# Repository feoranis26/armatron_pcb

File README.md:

## ARMATRON pcb
PCB prototype files for ARMATRON

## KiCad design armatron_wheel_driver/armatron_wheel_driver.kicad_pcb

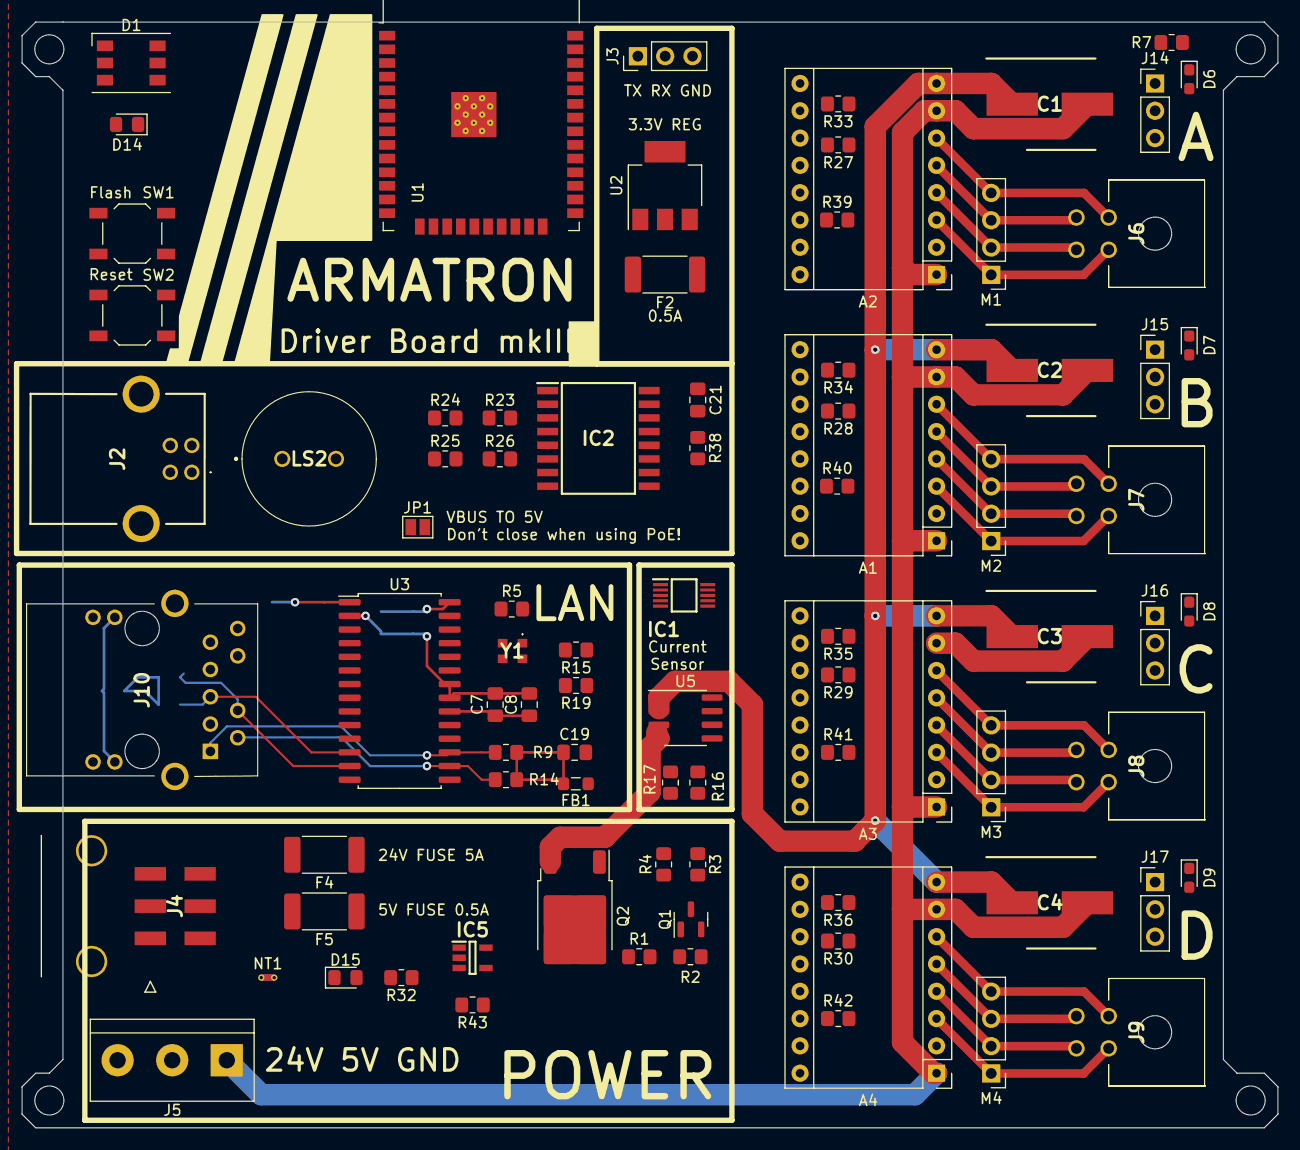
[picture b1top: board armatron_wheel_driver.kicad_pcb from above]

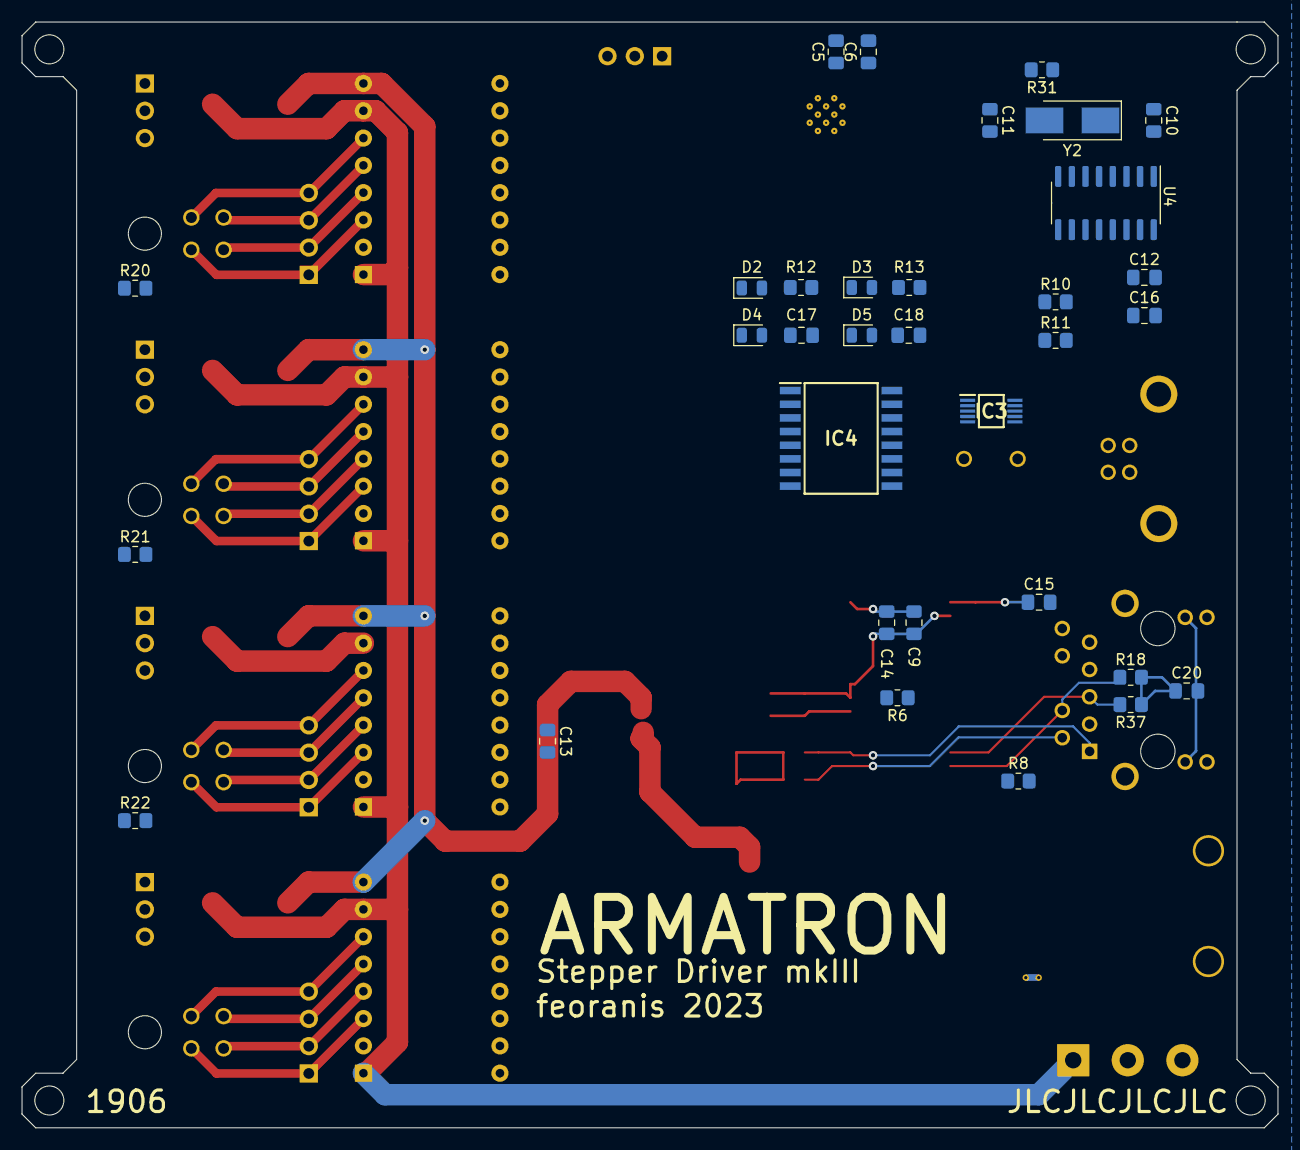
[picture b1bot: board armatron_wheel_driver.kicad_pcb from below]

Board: 2 copper layers, 116.8 x 102.9 mm, 123 parts (33 on the bottom side), 108 nets.

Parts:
A1, A2, A3, A4: Pololu_Breakout_DRV8825; Pololu_Breakout-16_15.2x20.3mm
C1, C2, C3, C4: C; CAPAE850X1050N
C5, C21: 10u; C_0805_2012Metric_Pad1.18x1.45mm_HandSolder
C6, C7, C9, C16, C17, C18: 100n; C_0805_2012Metric_Pad1.18x1.45mm_HandSolder
C8, C14, C15: 10uF; C_0805_2012Metric_Pad1.18x1.45mm_HandSolder
C10, C11: 22pF; C_0805_2012Metric_Pad1.18x1.45mm_HandSolder
C12: 4.7u; C_0805_2012Metric_Pad1.18x1.45mm_HandSolder
C13: 1n; C_0805_2012Metric_Pad1.18x1.45mm_HandSolder
C19, C20: 0.1uF; C_0805_2012Metric_Pad1.18x1.45mm_HandSolder
D1: Inolux_IN-PI556FCH; LED_WS2812_PLCC6_5.0x5.0mm_P1.6mm
D2, D3, D4, D5: D; D_0805_2012Metric
D6, D7, D8, D9: LED; LED_0603_1608Metric_Pad1.05x0.95mm_HandSolder
D14, D15: LED_Small; LED_0805_2012Metric_Pad1.15x1.40mm_HandSolder
F2, F5: 0.5A; Fuse_2512_6332Metric_Pad1.52x3.35mm_HandSolder
F4: 5A; Fuse_2512_6332Metric_Pad1.52x3.35mm_HandSolder
FB1: FerriteBead_Small; L_0805_2012Metric_Pad1.05x1.20mm_HandSolder
H1, H2, H3, H4: MountingHole; MountingHole_2.7mm_M2.5
IC1: ADS1115BQDGSRQ1; SOP50P490X110-10N
IC2, IC4: PCF8574T_3,518; SOIC127P1032X265-16N
IC3: MAX4634EUB+; SOP50P490X110-10N
IC5: M74VHC1GT50DTT1G; SOT95P275X110-5N
J2: USB_B; USB1030GFPBB
J3: Conn_01x03_Pin; PinHeader_1x03_P2.54mm_Vertical
J4: 43045-0606; 43045-06YY_060708_1
J5: Screw_Terminal_01x03; TerminalBlock_bornier-3_P5.08mm
J6, J7, J8, J9: 3-794620-4; 37946204
J10: 74982104400
J14, J15, J16, J17: Conn_01x03_Socket; PinHeader_1x03_P2.54mm_Vertical
JP1: SolderJumper_2_Open; SolderJumper-2_P1.3mm_Open_Pad1.0x1.5mm
LS2: PT-1241PFQ; PT1241PFQ
M1, M2, M3, M4: 17HS4401; PinHeader_1x04_P2.54mm_Vertical
NT1: NetTie_2; NetTie-2_THT_Pad0.3mm
Q1: BC817; SOT-23
Q2: Q_PNP_Darlington_BCE; TO-252-2
R1: 100K; R_0805_2012Metric_Pad1.20x1.40mm_HandSolder
R2, R3, R4, R7, R20, R21, R22, R23, R24, R25, R26, R27, R28, R29, R30, R31, R32, R33, R34, R35, R36, R38, R39, R40, R41, R42, R43: 1K; R_0805_2012Metric_Pad1.20x1.40mm_HandSolder
R5, R6, R10, R11, R12, R13: 10K; R_0805_2012Metric_Pad1.20x1.40mm_HandSolder
R8: 2.32K 1%; R_0805_2012Metric_Pad1.20x1.40mm_HandSolder
R9, R14, R18, R37: 50R; R_0805_2012Metric_Pad1.20x1.40mm_HandSolder
R15, R19: 220R; R_0805_2012Metric_Pad1.20x1.40mm_HandSolder
R16: 220K; R_0805_2012Metric_Pad1.20x1.40mm_HandSolder
R17: 27K; R_0805_2012Metric_Pad1.20x1.40mm_HandSolder
SW1, SW2: SW_Push; SW_SPST_TL3342
U1: ESP32-WROOM-32
U2: AMS1117-3.3; SOT-223-3_TabPin2
U3: ENC28J60x-SO; SOIC-28W_7.5x17.9mm_P1.27mm
U4: CH340G; SOIC-16_3.9x9.9mm_P1.27mm
U5: ACS712xLCTR-20A; SOIC-8_3.9x4.9mm_P1.27mm
Y1: ECS-2520MVLC-250-BN-TR3; ECS2520MVLC250BNTR3
Y2: 12MHz; Crystal_SMD_5032-2Pin_5.0x3.2mm_HandSoldering

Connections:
+3.3V: C5.1, C6.1, C7.1, C8.1, C9.1, C12.1, C14.1, C16.1, C21.1, D6.2 (A), D7.2 (A), D8.2 (A), D9.2 (A), D14.2 (A), F2.2, FB1.1, IC1.8 (VDD), IC2.16 (VDD), IC3.5 (EN), IC3.6 (V+), IC4.1 (A0), IC4.16 (VDD), IC5.5 (VCC), R5.1, R12.1, R13.1, R23.1, R24.1, R25.1, R26.1, R27.1, R28.1, R29.1, R30.1, R32.1, R38.1, R39.2, R40.2, R41.2, R42.2, R43.1, U1.2 (VDD), U3.15 (VDDTX), U3.19 (VDDRX), U3.20 (VDDPLL), U3.25 (VDDOSC), U3.28 (VDD), U4.4 (V3), U4.16 (VCC), Y1.4 (VDD)
+5V: D1.3 (VDD), D1.5 (VCC), F5.1, J5.2, J10.9 (V2+), J14.2, J15.2, J16.2, J17.2, JP1.2 (B), U2.3 (VI), U5.8 (VCC)
+24V: F4.1, J5.3, Q2.2 (C), R3.1, R16.1
/A_Assembly/A1: A2.4 (A1), J6.4, M1.2 (-)
/A_Assembly/A2: A2.3 (A2), J6.3, M1.1
/A_Assembly/B1: A2.5 (B1), J6.2, M1.3
/A_Assembly/B2: A2.6 (B2), J6.1, M1.4
/B_Assembly/A1: A1.4 (A1), J7.4, M2.2 (-)
/B_Assembly/A2: A1.3 (A2), J7.3, M2.1
/B_Assembly/B1: A1.5 (B1), J7.2, M2.3
/B_Assembly/B2: A1.6 (B2), J7.1, M2.4
/C_Assembly/A1: A3.4 (A1), J8.4, M3.2 (-)
/C_Assembly/A2: A3.3 (A2), J8.3, M3.1
/C_Assembly/B1: A3.5 (B1), J8.2, M3.3
/C_Assembly/B2: A3.6 (B2), J8.1, M3.4
/D_Assembly/A1: A4.4 (A1), J9.4, M4.2 (-)
/D_Assembly/A2: A4.3 (A2), J9.3, M4.1
/D_Assembly/B1: A4.5 (B1), J9.2, M4.3
/D_Assembly/B2: A4.6 (B2), J9.1, M4.4
/Ethernet/LEDA: R19.2, U3.27 (LEDA)
/Ethernet/LEDB: R15.2, U3.26 (LEDB)
/Ethernet/RX+: J10.4 (RD+), R18.1, U3.13 (TPIN+)
/Ethernet/RX-: J10.5 (RD-), R37.2, U3.12 (TPIN-)
/Ethernet/TPOUT+: J10.1 (TD+), R9.2, U3.17 (TPOUT+)
/Ethernet/TPOUT-: J10.2 (TD-), R14.1, U3.16 (TPOUT-)
/Ethernet/TX_CT: C19.1, FB1.2, J10.3 (CD), R9.1, R14.2
/USB/VBUS: J2.1 (VBUS), JP1.1 (A)
/USB/nDTR: R10.2, U4.13 (~DTR)
/USB/nRTS: R11.2, U4.14 (~RTS)
BL_DIR: A3.16 (DIR), U1.12 (IO27)
BL_STEP: A3.15 (STEP), U1.28 (IO17)
BR_DIR: A4.16 (DIR), U1.9 (IO33)
BR_STEP: A4.15 (STEP), U1.8 (IO32)
C_ADC: IC1.4 (AIN0), U5.7 (VIOUT)
ETH_CS: U1.29 (IO5), U3.9 (~CS)
ETH_INTER: U1.26 (IO4), U3.4 (~INT)
FLASH_UART: D3.1 (K), R10.1
FL_DIR: A2.16 (DIR), U1.10 (IO25)
FL_STEP: A2.15 (STEP), U1.16 (IO13)
FR_DIR: A1.16 (DIR), U1.11 (IO26)
FR_STEP: A1.15 (STEP), U1.27 (IO16)
GND: C5.2, C6.2, C7.2, C8.2, C9.2, C10.2, C11.2, C12.2, C13.2, C14.2, C15.2, C16.2, C17.2, C18.2, C19.2, C20.2, C21.2, D1.6 (VSS), IC1.1 (ADDR), IC1.3 (GND), IC2.1 (A0), IC2.2 (A1), IC2.3 (A2), IC2.8 (VSS), IC3.3 (GND), IC4.2 (A1), IC4.3 (A2), IC4.8 (VSS), IC5.3 (GND), J2.4 (GND), J3.3, J10.10 (V2-), J10.11 (A_GREEN/K_YELLOW_1), J10.13 (A_GREEN/K_YELLOW_2), J10.MH1, J10.MH2, J14.1, J15.1, J16.1, J17.1, LS2.1 (-), NT1.1, Q1.2 (E), R1.1, R6.1, R8.2, R17.2, R31.2, R33.1, R34.1, R35.1, R36.1, SW1.2, SW2.2, U1.1 (GND), U1.15 (GND), U1.38 (GND), U1.39 (GND), U2.1 (GND), U3.2 (VSS), U3.11 (VSSRX), U3.18 (VSSTX), U3.21 (VSSPLL), U3.22 (VSSOSC), U4.1 (GND), U5.5 (GND), Y1.2 (GND)
GNDPWR: A1.1 (GND), A1.7 (GND), A2.1 (GND), A2.7 (GND), A3.1 (GND), A3.7 (GND), A4.1 (GND), A4.7 (GND), C1.2, C2.2, C3.2, C4.2, J4.1, J4.2, J5.1, NT1.2
LIMIT_SW: IC3.8 (COM), U1.7 (IO35)
LIMIT_SWA: IC2.4 (P0), IC3.2 (NO1), J14.3, R7.2, R23.2
LIMIT_SWB: IC2.5 (P1), IC3.9 (NO2), J15.3, R20.2, R24.2
LIMIT_SWC: IC2.6 (P2), IC3.4 (NO3), J16.3, R21.2, R25.2
LIMIT_SWD: IC2.7 (P3), IC3.7 (NO4), J17.3, R22.2, R26.2
LS_INTR: IC2.13 (~INT), R38.2, U1.6 (IO34)
M1: A1.10 (M0), A2.10 (M0), A3.10 (M0), A4.10 (M0), IC2.9 (P4)
M2: A1.11 (M1), A2.11 (M1), A3.11 (M1), A4.11 (M1), IC2.10 (P5)
M3: A1.12 (M2), A2.12 (M2), A3.12 (M2), A4.12 (M2), IC2.11 (P6)
MISO: U1.31 (IO19), U3.6 (SO)
MOSI: U1.37 (IO23), U3.7 (SI)
MUX_A0: IC3.1 (A0), IC4.4 (P0)
MUX_A1: IC3.10 (A1), IC4.5 (P1)
NEOPIXEL: D1.2 (DIN), U1.24 (IO2)
unnamed: A1.9 (~EN), R34.2
unnamed: A1.13 (~RST), R28.2
unnamed: A2.9 (~EN), R33.2
unnamed: A2.13 (~RST), R27.2
unnamed: A3.9 (~EN), R35.2
unnamed: A3.13 (~RST), R29.2
unnamed: A4.9 (~EN), R36.2
unnamed: A4.13 (~RST), R30.2
unnamed: C20.1, R18.2, R37.1
unnamed: D4.1 (K), SW1.1
unnamed: D5.1 (K), SW2.1
unnamed: D6.1 (K), R7.1
unnamed: D7.1 (K), R20.1
unnamed: D8.1 (K), R21.1
unnamed: D9.1 (K), R22.1
unnamed: D14.1 (K), R31.1
unnamed: D15.2 (A), R32.2
unnamed: D15.1 (K), Q1.3 (C), R3.2, R4.1
unnamed: F4.2, J4.5, J4.6
unnamed: F5.2, J4.3
unnamed: IC1.5 (AIN1), R16.2, R17.1
unnamed: J2.3 (D+), U4.5 (UD+)
unnamed: J2.2 (D-), U4.6 (UD-)
unnamed: J10.12 (K_GREEN/A_YELLOW_1), R19.1
unnamed: J10.14 (K_GREEN/A_YELLOW_2), R15.1
unnamed: Q1.1 (B), R2.2
unnamed: Q2.1 (B), R4.2
unnamed: F2.1, U2.2 (VO)
unnamed: U3.23 (OSC1), Y1.3 (OUTPUT)
unnamed: R6.2, U3.24 (OSC2)
unnamed: R8.1, U3.14 (RBIAS)
unnamed: C15.1, U3.1 (VCAP)
unnamed: C10.1, U4.7 (XI), Y2.1
unnamed: C11.1, U4.8 (XO), Y2.2
unnamed: C13.1, U5.6 (FILTER)
unnamed: R5.2, Y1.1 (TRI-STATE)
PIEZO: LS2.2 (+), U1.14 (IO12)
PIN_FLASH: C18.1, D3.2 (A), D5.2 (A), R13.2, U1.25 (IO0)
PIN_RESET: C17.1, D2.2 (A), D4.2 (A), R12.2, U1.3 (EN), U3.10 (~RESET)
POWER_DETECT: IC4.6 (P2), J4.4, R43.2
POWER_EN: IC4.7 (P3), IC5.2 (INA)
POWER_EN_D: IC5.4 (OUT_Y), R1.2, R2.1
RESET_UART: D2.1 (K), R11.1
RX: J3.2, U1.34 (RXD0/IO3), U4.2 (TXD)
SCK: U1.30 (IO18), U3.8 (SCK)
SCL: IC1.10 (SCL), IC2.14 (SCL), IC4.14 (SCL), U1.36 (IO22)
SDA: IC1.9 (SDA), IC2.15 (SDA), IC4.15 (SDA), U1.33 (IO21)
SLP_DRIVERS: A1.14 (~SLP), A2.14 (~SLP), A3.14 (~SLP), A4.14 (~SLP), IC2.12 (P7), R39.1, R40.1, R41.1, R42.1
TX: J3.1, U1.35 (TXD0/IO1), U4.3 (RXD)
V_SENSE_IN: Q2.3 (E), U5.3 (IP-), U5.4 (IP-)
Vdrive: A1.8 (VMOT), A2.8 (VMOT), A3.8 (VMOT), A4.8 (VMOT), C1.1, C2.1, C3.1, C4.1, U5.1 (IP+), U5.2 (IP+)

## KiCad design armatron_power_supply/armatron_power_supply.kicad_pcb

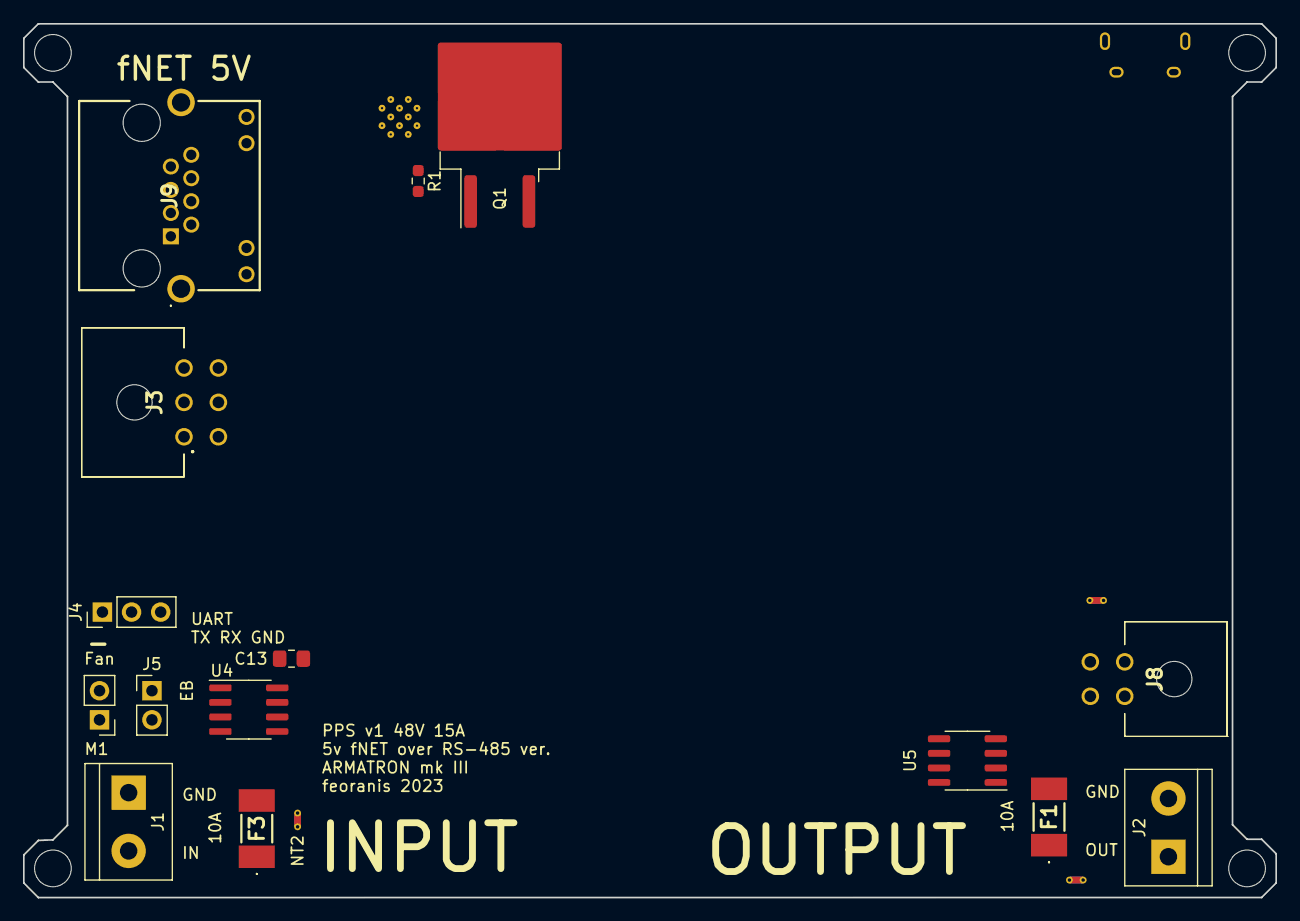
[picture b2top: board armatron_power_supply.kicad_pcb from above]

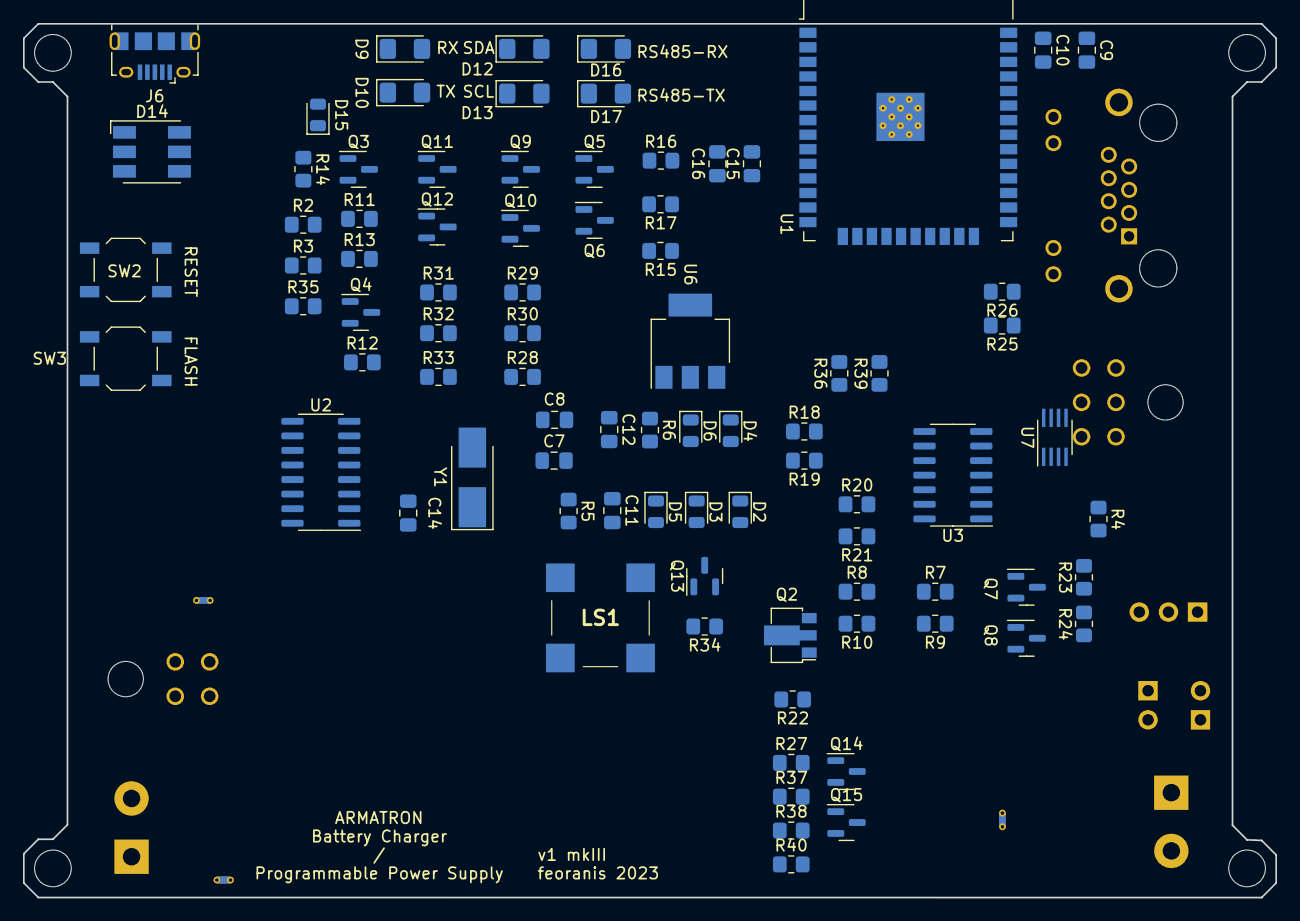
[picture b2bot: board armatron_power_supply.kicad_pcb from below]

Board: 4 copper layers, 109.2 x 76.2 mm, 107 parts (85 on the bottom side), 89 nets, no tracks yet.

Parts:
C7, C8: 22pF; C_0805_2012Metric_Pad1.18x1.45mm_HandSolder
C9: 4.7u; C_0805_2012Metric_Pad1.18x1.45mm_HandSolder
C10, C11, C12, C16: 100n; C_0805_2012Metric_Pad1.18x1.45mm_HandSolder
C13, C14: 1n; C_0805_2012Metric_Pad1.18x1.45mm_HandSolder
C15: 10u; C_0805_2012Metric_Pad1.18x1.45mm_HandSolder
D2, D3, D4, D5, D6, D15: D; D_0805_2012Metric
D9, D10, D12, D13, D16, D17: LED; LED_1206_3216Metric_Pad1.42x1.75mm_HandSolder
D14: LED_RGB; LED_RGB_5050-6
F1, F3: 0451010.MRL; 0451010MRL
J1, J2: Screw_Terminal_01x02; TerminalBlock_bornier-2_P5.08mm
J3: 3-794620-6; 37946206
J4: Conn_01x03_Pin; PinHeader_1x03_P2.54mm_Vertical
J5: Conn_01x02; PinHeader_1x02_P2.54mm_Vertical
J6: USB_B_Micro; USB_Micro-B_Amphenol_10118194_Horizontal
J8: 3-794620-4; 37946204
J9: SS-90000-009; SS90000009
LS1: CMT-8504-100-SMT-TR; CMT8504100SMTTR
M1: Fan; PinHeader_1x02_P2.54mm_Vertical
MH1, MH2, MH3, MH4: MountingHole_3.2mm_M3
NT1, NT2, NT3: NetTie_2; NetTie-2_THT_Pad0.3mm
Q1: IRF4905; TO-263-2
Q2: BCX56; SOT-89-3
Q3, Q4, Q5, Q6, Q7, Q8, Q9, Q10, Q11, Q12, Q13, Q14, Q15: BC817; SOT-23
R1: R; R_0603_1608Metric_Pad0.98x0.95mm_HandSolder
R2, R3, R35: 220R; R_0805_2012Metric_Pad1.20x1.40mm_HandSolder
R4, R16, R25, R26, R36, R39: 1K; R_0805_2012Metric_Pad1.20x1.40mm_HandSolder
R5, R6, R11, R12, R15, R17, R22, R23, R24, R27, R28, R29, R31, R32, R34, R37: 10K; R_0805_2012Metric_Pad1.20x1.40mm_HandSolder
R7, R8: 22K; R_0805_2012Metric_Pad1.20x1.40mm_HandSolder
R9, R10, R19, R21: 15K; R_0805_2012Metric_Pad1.20x1.40mm_HandSolder
R13, R14, R30, R33, R38, R40: 1k; R_0805_2012Metric_Pad1.20x1.40mm_HandSolder
R18, R20: 220K; R_0805_2012Metric_Pad1.20x1.40mm_HandSolder
SW2, SW3: SW_Push; SW_SPST_TL3342
U1: ESP32-WROOM-32
U2: CH340G; SOIC-16_3.9x9.9mm_P1.27mm
U3: MCP3428; SOIC-14_3.9x8.7mm_P1.27mm
U4, U5: ACS712xLCTR-20A; SOIC-8_3.9x4.9mm_P1.27mm
U6: AMS1117-3.3; SOT-223-3_TabPin2
U7: MAX485E; SSOP-8_2.95x2.8mm_P0.65mm
Y1: 12MHz; Crystal_SMD_5032-2Pin_5.0x3.2mm_HandSoldering

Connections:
+3.3V: C9.1, C10.1, C15.1, C16.1, D9.1 (K), D10.1 (K), D12.1 (K), D13.1 (K), D16.1 (K), D17.1 (K), R4.1, R5.1, R6.1, R29.2, R32.2, U1.2 (VDD), U2.4 (V3), U2.16 (VCC), U3.6 (VDD), U6.2 (VO)
+5V: D15.1 (K), J3.3, J9.4, J9.6, J9.8, LS1.1 (+), U4.8 (VCC), U5.8 (VCC), U6.3 (VI), U7.8 (VCC)
C_IN: F3.1, J1.2, J3.5, J3.6
C_OUT: F1.1, J2.1, J8.3, J8.4
D+: J6.3 (D+), U2.5 (UD+)
D-: J6.2 (D-), U2.6 (UD-)
EB: J5.1, R4.2, R15.1, U1.31 (IO19)
FLASH_UART: D4.1 (K), Q8.3 (C)
GND: C9.2, C10.2, C11.2, C12.2, C13.2, C14.2, C15.2, C16.2, J4.3, J5.2, J6.5 (GND), J6.6 (Shield), J9.3, J9.5, J9.9 (K_GREEN), J9.11 (K_YELLOW), NT1.2, Q2.3 (E), Q3.2 (E), Q4.2 (E), Q5.2 (E), Q6.2 (E), Q9.2 (E), Q10.2 (E), Q11.2 (E), Q12.2 (E), Q13.2 (E), Q14.2 (E), Q15.2 (E), R2.1, R3.1, R9.2, R10.2, R19.2, R21.2, R35.1, SW2.2, SW3.2, U1.1 (GND), U1.15 (GND), U1.38 (GND), U1.39 (GND), U2.1 (GND), U3.2 (CH1-), U3.4 (CH2-), U3.5 (VSS), U3.9 (Adr0), U3.10 (Adr1), U3.12 (CH3-), U3.14 (CH4-), U4.5 (GND), U5.5 (GND), U6.1 (GND), U7.5 (GND)
GND_PIN: J9.7, U1.8 (IO32)
IN: F3.2, NT2.2, U4.3 (IP-), U4.4 (IP-)
LED_1A: R26.2, U1.13 (IO14)
LED_1B: R25.2, U1.16 (IO13)
unnamed: D5.1 (K), SW2.1
unnamed: D6.1 (K), SW3.1
unnamed: D9.2 (A), R13.2
unnamed: D10.2 (A), R14.2
unnamed: D12.2 (A), R30.2
unnamed: D13.2 (A), R33.2
unnamed: D14.4 (BK), R35.2
unnamed: D14.6 (GK), R3.2
unnamed: D14.5 (RK), R2.2
unnamed: D16.2 (A), R38.2
unnamed: D17.2 (A), R40.2
unnamed: J9.10 (A_GREEN), R26.1
unnamed: J9.12 (A_YELLOW), R25.1
unnamed: LS1.2 (-), Q13.3 (C)
unnamed: M1.2 (-), Q2.2 (C)
unnamed: NT2.1, R18.1
unnamed: NT3.1, R20.1
unnamed: Q2.1 (B), R22.1
unnamed: Q3.1 (B), R11.2
unnamed: Q3.3 (C), R13.1
unnamed: Q4.1 (B), R12.2
unnamed: Q4.3 (C), R14.1
unnamed: Q5.1 (B), R15.2
unnamed: Q5.3 (C), R16.1
unnamed: Q6.1 (B), R16.2, R17.2
unnamed: Q7.1 (B), R23.2
unnamed: Q8.1 (B), R24.2
unnamed: Q9.1 (B), R28.2
unnamed: Q9.3 (C), Q10.1 (B), R29.1
unnamed: Q10.3 (C), R30.1
unnamed: Q11.1 (B), R31.2
unnamed: Q11.3 (C), Q12.1 (B), R32.1
unnamed: Q12.3 (C), R33.1
unnamed: Q13.1 (B), R34.2
unnamed: Q14.1 (B), R27.2
unnamed: Q14.3 (C), R38.1
unnamed: Q15.1 (B), R37.2
unnamed: Q15.3 (C), R40.1
unnamed: C7.1, U2.7 (XI), Y1.1
unnamed: C8.1, U2.8 (XO), Y1.2
unnamed: C13.1, U4.6 (FILTER)
unnamed: C14.1, U5.6 (FILTER)
OUT: F1.2, NT3.2, U5.1 (IP+), U5.2 (IP+)
PGND: J1.1, J2.2, J3.1, J3.2, J8.1, J8.2, NT1.1
PIN_BATT_B_SENSE_ADC: R7.2, R9.1
PIN_BUZZER: R34.1, U1.36 (IO22)
PIN_FLASH: C12.1, D4.2 (A), D6.2 (A), R6.2, U1.25 (IO0)
PIN_Fan: R22.2, U1.33 (IO21)
PIN_RESET: C11.1, D2.2 (A), D3.2 (A), D5.2 (A), R5.2, U1.3 (EN)
PIN_RGB_B: D14.3 (BA), U1.10 (IO25)
PIN_RGB_G: D14.1 (GA), U1.37 (IO23)
PIN_RGB_R: D14.2 (RA), U1.23 (IO15)
PIN_VIN_SENSE: R8.1, U3.1 (CH1+), U4.7 (VIOUT)
PIN_VIN_SENSE_ADC: R8.2, R10.1
PIN_VOUT_SENSE: U3.3 (CH2+), U5.7 (VIOUT)
RESET_UART: D2.1 (K), Q7.3 (C)
RS485_A: J9.1, U7.6 (A)
RS485_B: J9.2, U7.7 (B)
RS485_DE: U7.2 (~RE), U7.3 (DE)
RS485_RX: R27.1, R36.1, U1.27 (IO16)
RS485_RX_H: R36.2, U7.1 (RO)
RS485_TX: R37.1, R39.1, U1.28 (IO17)
RS485_TX_H: R39.2, U7.4 (DI)
RX: J4.2, R11.1, U1.34 (RXD0/IO3), U2.2 (TXD)
SCL: R31.1, U1.12 (IO27), U3.8 (SCL)
SDA: R28.1, U1.11 (IO26), U3.7 (SDA)
SW: Q1.1 (G), Q6.3 (C), R1.2
SWITCH_PIN: R17.1, U1.30 (IO18)
TX: J4.1, R12.1, U1.35 (TXD0/IO1), U2.3 (RXD)
VBUS: D15.2 (A), J6.1 (VBUS)
VIN: Q1.2 (D), R1.1, U4.1 (IP+), U4.2 (IP+)
VIN_ADC: R18.2, R19.1, U3.11 (CH3+)
VOUT: U5.3 (IP-), U5.4 (IP-)
VOUT_ADC: R20.2, R21.1, U3.13 (CH4+)
nDTR: Q8.2 (E), R23.1, U2.13 (~DTR)
nRTS: Q7.2 (E), R24.1, U2.14 (~RTS)
